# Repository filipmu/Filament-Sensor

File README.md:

# Filament-Sensor
A sensor that measures with width of filament for 3D printers

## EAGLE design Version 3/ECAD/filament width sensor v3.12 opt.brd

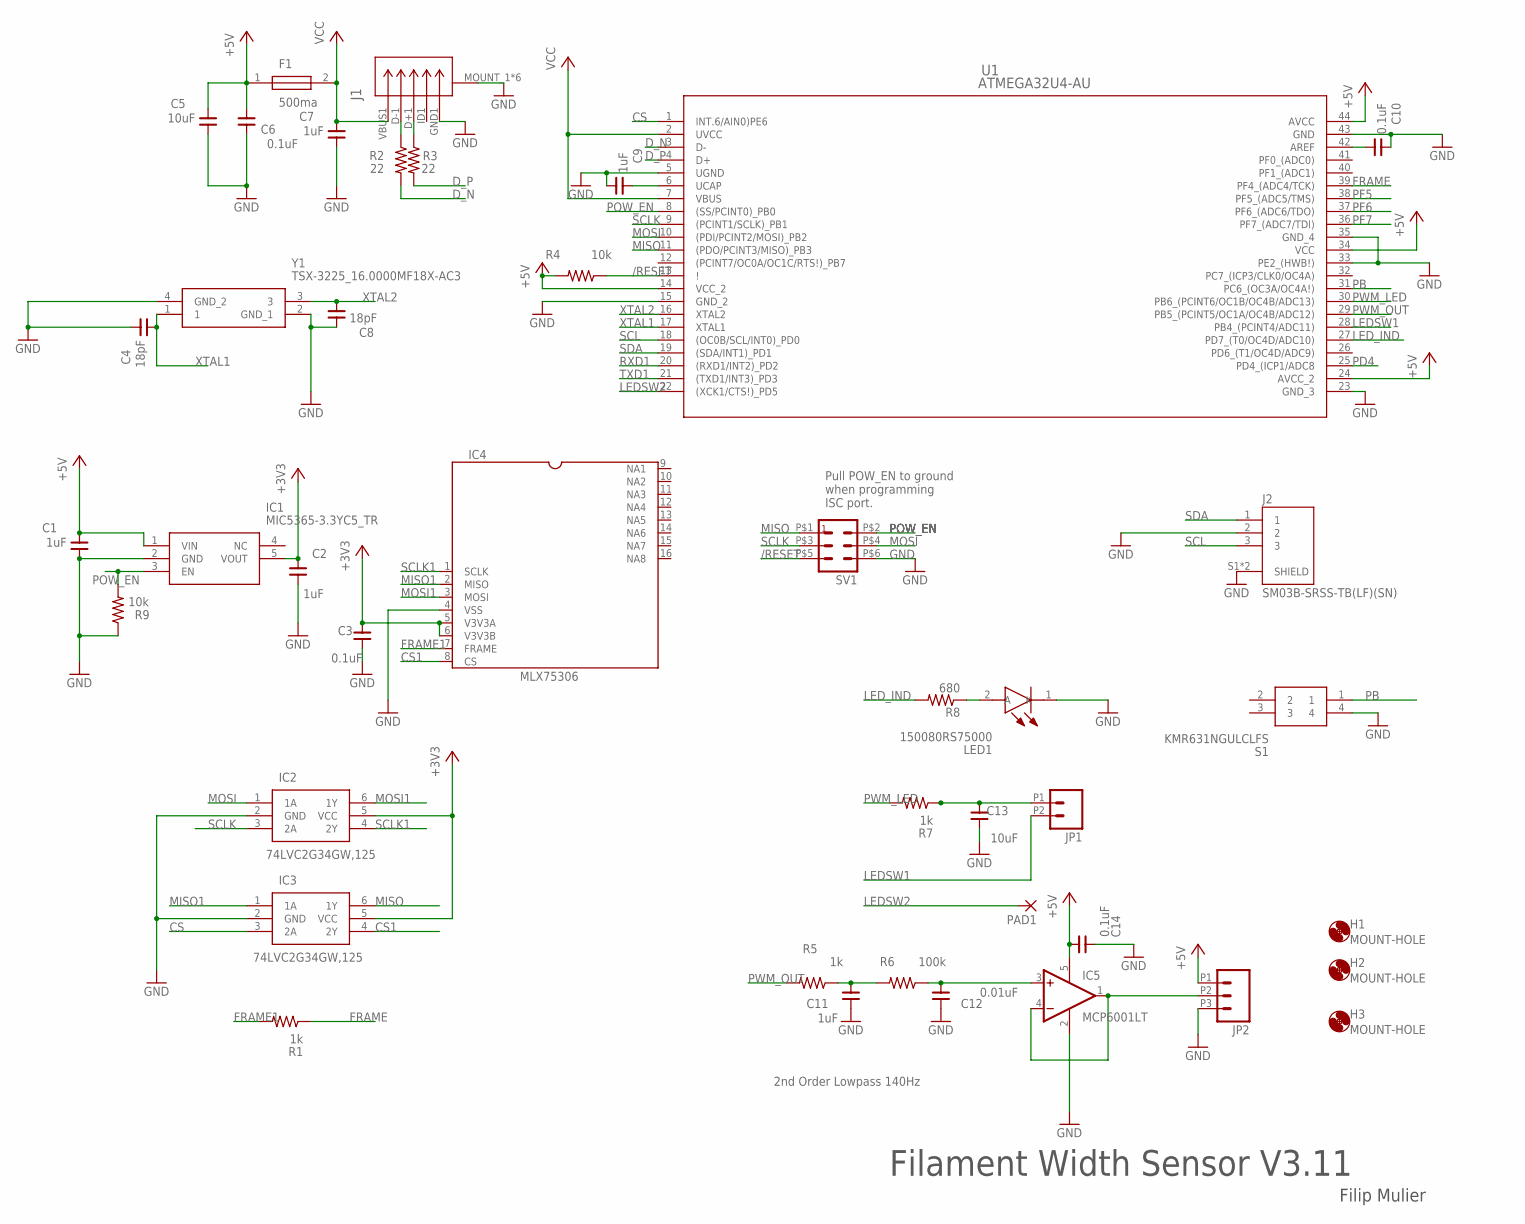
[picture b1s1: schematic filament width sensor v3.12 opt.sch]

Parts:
C1, C2, C7, C9, C11: 1uF; 0603
C3, C6, C10, C14: 0.1uF; 0603
C4, C8: 18pF; 0603
C5, C13: 10uF; 0805
C12: 0.01uF; 0603
F1: 500ma; FUSC3216X75N
H1, H2, H3: MOUNT-HOLE; SCREWHOLE2-56
IC1: MIC5365-3.3YC5_TR; SOT65P210X110-5N
IC2, IC3: 74LVC2G34GW,125; SOP65P210X110-6N
IC4: MLX75306; SO16NBC
IC5: MCP6001LT; MCP6001_SC70-5
J1: USB; CONN5_ZX62D-B-5PA8_HIR
J2: SM03B-SRSS-TB(LF)(SN); JST_SM03B-SRSS-TB(LF)(SN)
JP1: M022.54MM_SCREWTERM; 1X02_2.54_SCREWTERM
JP2: M03SCREW2.54; 1X03_2.54_SCREWTERM
LED1: 150080RS75000; LEDC2012X80N
PAD1: WIREPAD1,6/0,8; 1,6/0,8
R1, R5, R7: 1k; R0603
R2, R3: 22; R0603
R4, R9: 10k; R0603
R6: 100k; R0603
R8: 680; R0603
S1: KMR631NGULCLFS; KMR621NG
SV1: MA03-2SMD; MA03-2SMT
U1: ATMEGA32U4-AU; 44ML_ATM
Y1: TSX-3225_16.0000MF18X-AC3; TSX-3225V

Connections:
+3V3: C2.2, C3.2, IC1.5 (VOUT), IC2.5 (VCC), IC3.5 (VCC), IC4.5 (V3V3A), IC4.6 (V3V3B)
+5V: C1.2, C5.2, C6.2, C14.2, F1.1, IC1.1 (VIN), IC5.5 (V+), JP2.P1 (1), R4.2, U1.14 (VCC_2), U1.24 (AVCC_2), U1.34 (VCC), U1.44 (AVCC)
/RESET: R4.1, SV1.P$5 (5), U1.13 (!)
ADC9: IC5.1 (OUT), IC5.4 (-IN), JP2.P2 (2)
CS: IC3.3 (2A), U1.1 (INT.6/AIN0)PE6)
CS1: IC3.4 (2Y), IC4.8 (CS)
D1_N: J1.D+1, R3.1
D1_P: J1.D-1, R2.1
D_N: R2.2, U1.3 (D-)
D_P: R3.2, U1.4 (D+)
FRAME: R1.1, U1.39 (PF4_(ADC4/TCK))
FRAME1: IC4.7 (FRAME), R1.2
GND: C1.1, C2.1, C3.1, C4.2, C5.1, C6.1, C7.1, C8.2, C9.1, C10.2, C11.1, C12.1, C13.1, C14.1, IC1.2 (GND), IC2.2 (GND), IC3.2 (GND), IC4.4 (VSS), IC5.2 (V-), J1.GND1, J1.MOUNT_1 (CASE_GND), J1.MOUNT_2 (CASE_GND), J1.MOUNT_3 (CASE_GND), J1.MOUNT_4 (CASE_GND), J1.PAD_1 (CASE_GND), J1.PAD_2 (CASE_GND), J2.2, J2.S1 (SHIELD), J2.S2 (SHIELD), JP2.P3 (3), LED1.1 (K), R9.1, S1.4, SV1.P$6 (6), U1.5 (UGND), U1.15 (GND_2), U1.23 (GND_3), U1.33 (PE2_(HWB!)), U1.35 (GND_4), U1.43 (GND), Y1.2 (GND_1), Y1.4 (GND_2)
LEDSW1: JP1.P2 (2), U1.28 (PB4_(PCINT4/ADC11))
LEDSW2: PAD1.1, U1.22 ((XCK1/CTS!)_PD5)
LED_IND: R8.2, U1.27 (PD7_(T0/OC4D/ADC10))
MISO: IC3.6 (1Y), SV1.P$1 (1), U1.11 ((PDO/PCINT3/MISO)_PB3)
MISO1: IC3.1 (1A), IC4.2 (MISO)
MOSI: IC2.1 (1A), SV1.P$4 (4), U1.10 ((PDI/PCINT2/MOSI)_PB2)
MOSI1: IC2.6 (1Y), IC4.3 (MOSI)
unnamed: C9.2, U1.6 (UCAP)
unnamed: C10.1, U1.42 (AREF)
unnamed: C13.2, JP1.P1 (1), R7.1
unnamed: C11.2, R5.1, R6.2
unnamed: C12.2, IC5.3 (+IN), R6.1
unnamed: LED1.2 (A), R8.1
PB: S1.1, U1.31 (PC6_(OC3A/OC4A!))
PD4: U1.25 (PD4_(ICP1/ADC8)
PF5: U1.38 (PF5_(ADC5/TMS))
PF6: U1.37 (PF6_(ADC6/TDO))
PF7: U1.36 (PF7_(ADC7/TDI))
POW_EN: IC1.3 (EN), R9.2, SV1.P$2 (2), U1.8 ((SS/PCINT0)_PB0)
PWM_LED: R7.2, U1.30 (PB6_(PCINT6/OC1B/OC4B/ADC13))
PWM_OUT: R5.2, U1.29 (PB5_(PCINT5/OC1A/OC4B/ADC12))
RXD1: U1.20 ((RXD1/INT2)_PD2)
SCL: J2.3, U1.18 ((OC0B/SCL/INT0)_PD0)
SCLK: IC2.3 (2A), SV1.P$3 (3), U1.9 ((PCINT1/SCLK)_PB1)
SCLK1: IC2.4 (2Y), IC4.1 (SCLK)
SDA: J2.1, U1.19 ((SDA/INT1)_PD1)
TXD1: U1.21 ((TXD1/INT3)_PD3)
VCC: C7.2, F1.2, J1.VBUS1, U1.2 (UVCC), U1.7 (VBUS)
XTAL1: C4.1, U1.17 (XTAL1), Y1.1
XTAL2: C8.1, U1.16 (XTAL2), Y1.3

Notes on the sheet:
Filament Width Sensor V3.11
Filip Mulier
Pull POW_EN to ground when programming ISC port.
2nd Order Lowpass 140Hz

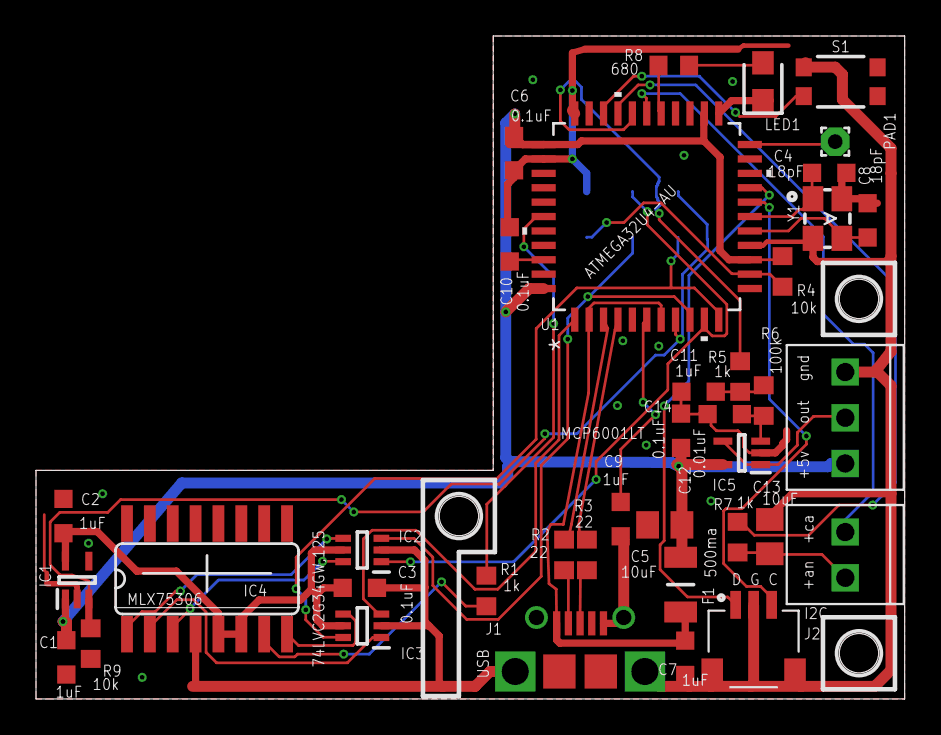
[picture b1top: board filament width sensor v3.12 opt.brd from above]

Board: 2 copper layers, 48.3 x 36.8 mm, 42 parts (1 on the bottom side), 37 nets.
